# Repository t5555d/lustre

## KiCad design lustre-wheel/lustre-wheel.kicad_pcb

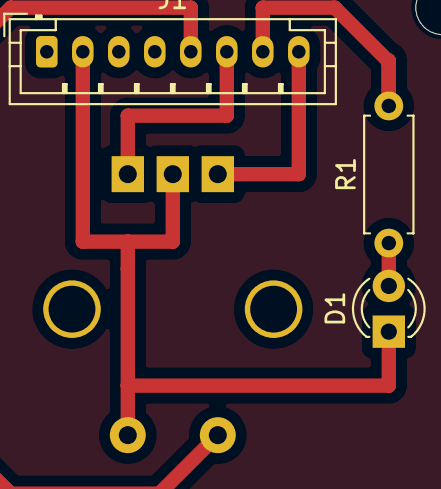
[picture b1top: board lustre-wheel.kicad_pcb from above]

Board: 2 copper layers, 4 parts (1 on the bottom side), 6 nets.

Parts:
D1: IR204A; LED_D3.0mm_IRBlack
J1: Conn_01x08_Pin; JST_PH_B8B-PH-K_1x08_P2.00mm_Vertical
R1: R; R_Axial_DIN0207_L6.3mm_D2.5mm_P7.62mm_Horizontal
SW1: RotaryEncoder_Switch; RotaryEncoder_Alps_EC11E-Switch_Vertical_H20mm_CircularMoun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

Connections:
unnamed: D1.2 (A), R1.1
unnamed: D1.1 (K), J1.2, SW1.S2, SW1.у (C)
unnamed: J1.5, SW1.S1
unnamed: J1.6, SW1.у (A)
unnamed: J1.7, R1.2
unnamed: J1.8, SW1.B

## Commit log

2025-08-13 add lustre-wheel scheme and pcb
